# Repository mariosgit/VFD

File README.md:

# VFD

A collection of upcycling projects for Vakuum Fluorescent Displays (VFD). These are Display as you may find in Audio/Video gear like CD/DVD players. A VFD requires high voltage to control anodes and gates, and a small AC voltage for the fillament(heater). To drive each single display element, a time multiplexed controller is required.

## Project Structure...

This is a playground for testing VFDs and there are the PCBs in PCB-KiCAD. See below..

If you only want the display drivers, check out the external repos which are submoduled in the ```./lib``` folder.

```lib/...``` containes submodule display libs and maybe some other local libs which are in development. If a stable status is reached I move them into their own repo.

```src/VFD_TPIC..``` stuff was not integrated into this platformio project yet..

```src/PanelDemo``` is a simple example for a VFD + encoder and button inputs.

```src/FreeDSPController``` is like PanelDemo + it reads some data via I2C from a FreeDSP/ADSP1701. It's a first experiment to use the code generated by SigmaStudio.

### Software Testing

So this is "just" a wrapper PlatformIO project which allows quick switching between the displays I work on.

The thing to be build can be choosen in ```.env``` file. If there is none, copy the ```.env.example```.

### src/main

Is a wrapper into the other sources under ```src``` or into the examples under ```lib/XYZ/examples/...```.

You can also switch between demo programms by commenting in/out the defines.. only one at a time... but using ```.env``` does not infect the git repo.

## PCBs

There are some sub-schematics like VFD-Power which are included in the other schematics.

### MN12832JC-TeensyLC

This is a VFD + 2 Encoders + 2 Switches. (For the FreeDSPController)

Status: Works somewhat, It would have been better with Level shifters. During power up it can show some random noise, due to level issues.

### GP1294AI

This is a board with the VFD + 2 encoders + 10 switches.

#### Status: Experimental, PCB is in development. 

Has some bugs, I2C and I2S on wrong pins... etc.

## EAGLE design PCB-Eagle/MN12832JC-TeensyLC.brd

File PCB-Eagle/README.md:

# Todo:

- Add Power Management
    - PowerSupply (12-24V) -> 5V Step Down Conv.
    - ON/OFF ? at least for the AMPs, or use sleep pins.
- Inputs via 74165 and SPI ? 3+2 Wires (MISO,CLK,LD, NxCE) (see PreenFM/Shruti)
- Add fancy lights
  - Teensy LC has a output for WS2812 (not 3.2, buffer 74LV1T125)
  - Around the encoders - glowing circle.
  - above and below the display

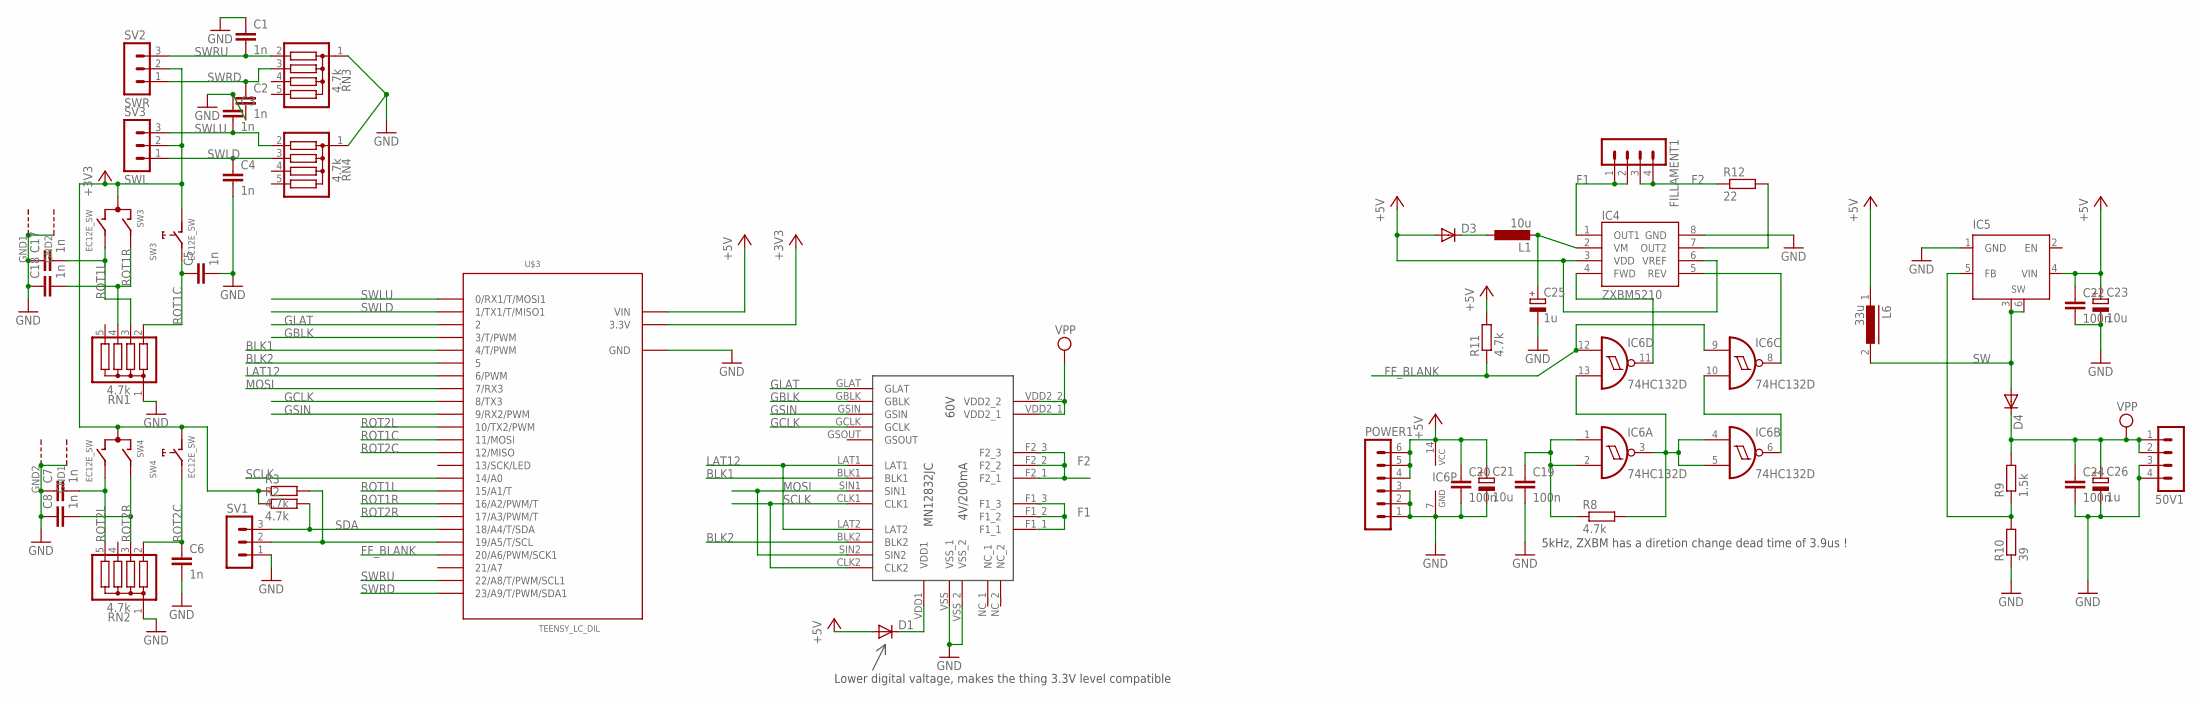
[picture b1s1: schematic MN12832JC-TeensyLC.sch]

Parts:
50V1: MA04-1
C1, C2, C3, C4, C5, C6, C7, C8, C17, C18: 1n; C1206
C19, C20, C22, C24: 100n; C1206
C21, C23: 10u; 153CLV-0807
C25, C26: 1u; 153CLV-0505
D1, D3, D4: DIODE-SMB; SMB
FILLAMENT1: MA04-1
IC4: ZXBM5210; SO8
IC5: XL6009; TO263-5
IC6: 74HC132D; SO14
L1: 10u; L1812
L6: 33u; DR125
POWER1: MA06-1
R2, R3, R8, R11: 4.7k; R1206
R9: 1.5k; R1206
R10: 39; R1206
R12: 22; 0411/15
RN1, RN2, RN3, RN4: 4.7k; SIL5
SV1: MA03-1
SV2: SWR; MA03-1
SV3: SWL; MA03-1
SW3, SW4: EC12E_SW; ALPS_EC12E_SW
U$1: MN12832JC
U$3: TEENSY_LC_DIL; TEENSY_3.0-3.2&LC_DIL

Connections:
+3V3: R2.1, R3.1, SV2.2, SV3.2, SW3.C, SW3.D (1), SW4.C, SW4.D (1), U$3.3.3V
+5V: C20.1, C21.+, C22.1, C23.+, D1.A, D3.A, IC4.3 (VDD), IC4.6 (VREF), IC5.4 (VIN), IC6.14 (VCC), L6.1, POWER1.4, POWER1.5, POWER1.6, R11.2, U$3.VIN
BLK1: U$1.BLK1, U$3.4 (4/T/PWM)
BLK2: U$1.BLK2, U$3.5
F1: FILLAMENT1.1, FILLAMENT1.2, IC4.1 (OUT1), U$1.F1_1, U$1.F1_2, U$1.F1_3
F2: FILLAMENT1.3, FILLAMENT1.4, R12.1, U$1.F2_1, U$1.F2_2, U$1.F2_3
FF_BLANK: IC6.9 (I0), IC6.12 (I0), R11.1, U$3.20/A6 (20/A6/PWM/SCK1)
GBLK: U$1.GBLK, U$3.3 (3/T/PWM)
GCLK: U$1.GCLK, U$3.8 (8/TX3)
GLAT: U$1.GLAT, U$3.2
GND: 50V1.3, 50V1.4, C1.1, C2.2, C3.1, C4.2, C5.2, C6.2, C7.1, C8.1, C17.1, C18.1, C19.2, C20.2, C21.-, C22.2, C23.-, C24.2, C25.-, C26.-, IC4.8 (GND), IC5.1 (GND), IC6.7 (GND), POWER1.1, POWER1.2, POWER1.3, R10.1, RN1.1, RN2.1, RN3.1, RN4.1, SV1.1, SW3.GND1 (G), SW3.GND2 (G), SW4.GND1 (G), SW4.GND2 (G), U$1.VSS (VSS_1), U$1.VSS_2, U$3.AGND (GND), U$3.GND
GSIN: U$1.GSIN, U$3.9 (9/RX2/PWM)
LAT12: U$1.LAT1, U$1.LAT2, U$3.6 (6/PWM)
MOSI: U$1.SIN1, U$1.SIN2, U$3.7 (7/RX3)
unnamed: D1.C, U$1.VDD1
unnamed: C19.1, IC6.1 (I0), IC6.2 (I1), R8.1
unnamed: IC4.5 (REV), IC6.8 (O)
unnamed: D3.C, L1.1
unnamed: C25.+, IC4.2 (VM), L1.2
unnamed: IC6.3 (O), IC6.4 (I0), IC6.5 (I1), IC6.13 (I1), R8.2
unnamed: IC5.5 (FB), R9.1, R10.2
unnamed: IC6.6 (O), IC6.10 (I1)
unnamed: IC4.4 (FWD), IC6.11 (O)
unnamed: IC4.7 (OUT2), R12.2
ROT1C: C5.1, RN1.2, SW3.E (2), U$3.11 (11/MOSI)
ROT1L: C17.2, RN1.3, SW3.B, U$3.15/A1 (15/A1/T)
ROT1R: C18.2, RN1.4, SW3.A, U$3.16/A2 (16/A2/PWM/T)
ROT2C: C6.1, RN2.2, SW4.E (2), U$3.12 (12/MISO)
ROT2L: C7.2, RN2.5, SW4.B, U$3.10 (10/TX2/PWM)
ROT2R: C8.2, RN2.3, SW4.A, U$3.17/A3 (17/A3/PWM/T)
SCL: R3.2, SV1.2, U$3.19/A5 (19/A5/T/SCL)
SCLK: U$1.CLK1, U$1.CLK2, U$3.14/A0
SDA: R2.2, SV1.3, U$3.18/A4 (18/A4/T/SDA)
SW: D4.A, IC5.3 (SW), IC5.6 (SW), L6.2
SWLD: C4.1, RN4.3, SV3.1, U$3.1 (1/TX1/T/MISO1)
SWLU: C3.2, RN4.2, SV3.3, U$3.0 (0/RX1/T/MOSI1)
SWRD: C2.1, RN3.3, SV2.1, U$3.23/A9 (23/A9/T/PWM/SDA1)
SWRU: C1.2, RN3.2, SV2.3, U$3.22/A8 (22/A8/T/PWM/SCL1)
VPP: 50V1.1, 50V1.2, C24.1, C26.+, D4.C, R9.2, U$1.VDD2_1, U$1.VDD2_2

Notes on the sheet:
5kHz, ZXBM has a diretion change dead time of 3.9us !
Lower digital valtage, makes the thing 3.3V level compatible

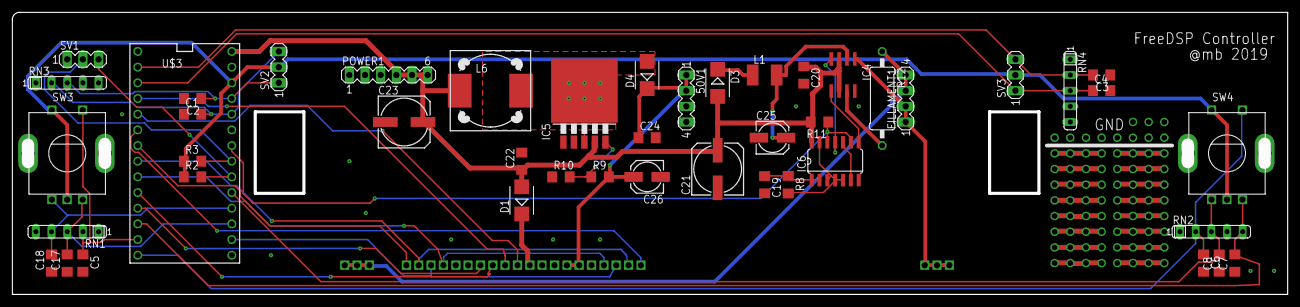
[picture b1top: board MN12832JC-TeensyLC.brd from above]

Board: 2 copper layers, 206.7 x 45.7 mm, 47 parts (1 on the bottom side), 39 nets.

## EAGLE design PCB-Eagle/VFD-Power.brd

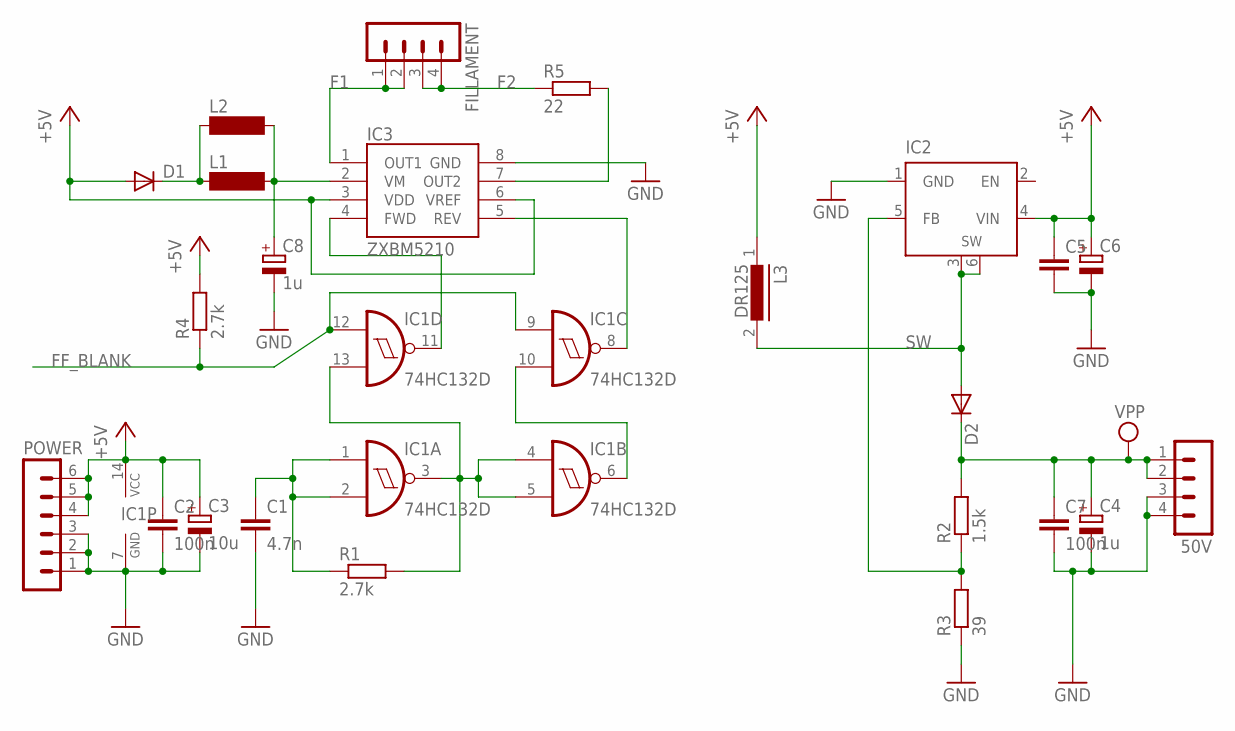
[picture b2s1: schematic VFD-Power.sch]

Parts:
50V: MA04-1
C1: 4.7n; C1206
C2, C7: 100n; C1206
C3: 10u; 153CLV-0807
C4, C8: 1u; 153CLV-0505
C5: C-EUC1206; C1206
C6: CPOL-EU153CLV-0807; 153CLV-0807
D1, D2: DIODE-SMB; SMB
FILLAMENT: MA04-1
IC1: 74HC132D; SO14
IC2: XL6009; TO263-5
IC3: ZXBM5210; SO8
L1: SM-NE45
L2: MS85
L3: DR125
POWER: MA06-1
R1, R4: 2.7k; R1206
R2: 1.5k; R1206
R3: 39; R1206
R5: 22; 0411/15

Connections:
+5V: C2.1, C3.+, C5.1, C6.+, D1.A, IC1.14 (VCC), IC2.4 (VIN), IC3.3 (VDD), IC3.6 (VREF), L3.1, POWER.4, POWER.5, POWER.6, R4.2
F1: FILLAMENT.1, FILLAMENT.2, IC3.1 (OUT1)
F2: FILLAMENT.3, FILLAMENT.4, R5.1
FF_BLANK: IC1.9 (I0), IC1.12 (I0), R4.1
GND: 50V.3, 50V.4, C1.2, C2.2, C3.-, C4.-, C5.2, C6.-, C7.2, C8.-, IC1.7 (GND), IC2.1 (GND), IC3.8 (GND), POWER.1, POWER.2, POWER.3, R3.1
unnamed: IC1.6 (O), IC1.10 (I1)
unnamed: C1.1, IC1.1 (I0), IC1.2 (I1), R1.1
unnamed: IC1.11 (O), IC3.4 (FWD)
unnamed: IC3.7 (OUT2), R5.2
unnamed: IC1.8 (O), IC3.5 (REV)
unnamed: D1.C, L1.1, L2.1
unnamed: C8.+, IC3.2 (VM), L1.2, L2.2
unnamed: IC1.3 (O), IC1.4 (I0), IC1.5 (I1), IC1.13 (I1), R1.2
unnamed: IC2.5 (FB), R2.1, R3.2
SW: D2.A, IC2.3 (SW), IC2.6 (SW), L3.2
VPP: 50V.1, 50V.2, C4.+, C7.1, D2.C, R2.2

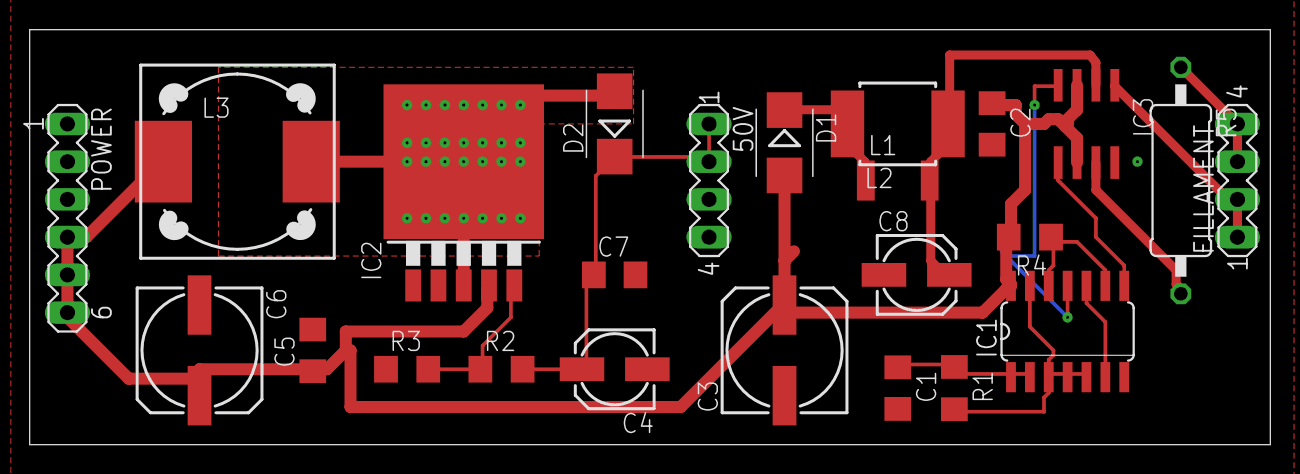
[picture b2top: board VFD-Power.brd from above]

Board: 2 copper layers, 83.5 x 27.9 mm, 24 parts (0 on the bottom side), 16 nets.

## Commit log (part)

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2018-04-25 Initial test program for TPIC6b595.
2018-04-25 Copy of the TPIC code for NEC FIP20D9X
2018-04-26 Update README.md
    Added instructable link.
2018-10-01 A bit more detail..
2018-10-28 It works.
2018-10-28 added image
2018-10-28 moved image
2018-10-28 Added Log lib, used here and there.
2018-10-28 Bit more Doc.
2018-10-28 Optimized, shorter interrupt, brighter display.
2019-01-07 Added some drawing demo code.
2019-01-08 First Attempt to use a STM32F1x. Experimenting with a MN12864.
2019-01-08 Ignore .vscode.
2019-11-10 Added PCBs.
2019-11-10 working on BOM
2019-11-19 Larger Drills for Display
2019-11-19 locked proto area, will not ripup and disappear
2019-11-20 minor stuff
2019-11-20 fixed Up Converter R9/R10 twist, adjusted values for 50V
2019-11-21 set PWM pin to high for the new board.
2019-11-22 Added Voltage drop diode for Vdd1, lowered Fillament frequency to avoid off time
2019-11-26 adapted for use with the AMP1, inital working version
2019-12-01 Rearanged in a bit more Arduino library style.
2019-12-01 sorted out example code vs. Panel code.
2019-12-04 added FreeDSP controller. Reads Levels. Sets Volume.
2019-12-04 LevelMeter+Volume
2019-12-04 Typo, Libpath
2019-12-04 updated readme...
2019-12-04 nicer
2019-12-04 todo list...
2019-12-04 more todo
2019-12-09 Waiting for I2C silence after boot.
2024-01-08 Freedom for makers !
2024-01-08 kicad ignore update.
2024-01-10 Progress on GP1294 board..
2024-01-15 GP1294 progress..
2024-01-16 GP1294 progress...
2024-01-18 GP1294...
2024-01-18 GP1294 more progress...
2024-01-21 more progress
2024-01-22 GP12.. better case and stuff
2024-01-23 ATtiny software for input control.
2024-01-29 GP1294 evolves
2024-01-31 Starting GP1294 software
2024-01-31 GP1294 stuff..
2024-02-01 Added SRC.
2024-02-01 grummel
2024-02-01 Fixed merge issues.
2024-02-02 nix.
2024-02-08 Added OLED 5.5" option
2024-02-09 Upgraded Power circuit.
2024-02-09 Added test code for GP1294
2024-02-12 Added Debounce Caps and stuff.
2024-02-15 README updated, restructuring..
2024-02-15 Rearranged into PlatformIO project.
2024-02-15 missing peaces..
2024-02-15 Experiments with MN12832L...
2024-02-16 Progress...
2024-02-16 Added Odd/Even buffers.
2024-02-16 Breakpoint, looking better, but only one gate active.
2024-02-16 Breakpoint, ok, just the seams...
2024-02-16 Nicer Demo
2024-02-16 Somewhat useable...
2024-02-19 Replaced dualbuffer with masking.
2024-02-19 Added doubl buffer.
2024-02-19 Runs with serial 1->2 chain.
2024-02-19 breakpoint, shift out 2x for serial in chain.
2024-02-19 Added greyscale.
2024-02-19 README merge.
2024-02-19 Moved MN12832L to own repo.
2024-02-19 still..
2024-02-19 Updated README.
2024-02-21 Progress with MN12832L...
2024-02-22 Compile on STM32
2024-02-22 Working on MN12864K...
2024-02-23 Experiments with MN12864K...
2024-02-23 Can change build example by .env file.
2024-02-23 Not much..
2024-02-23 Cleaned up readme.
2024-02-23 Stuff
2024-02-23 Fixing git..
2024-02-23 Readded subrepo.
2024-02-23 Readded subrepo 2
2024-02-23 Progress with MN12864K.
2024-02-26 drawFastHLine...
2024-02-26 Cleanup.
2024-02-26 Better.
2024-02-28 Added lib/font and example under MN12832L
2024-03-05 PCB: TestPin must pull up with 100k.
2024-03-05 More GP1294 experiments and stuff.
2024-03-06 Nicer Demo.
2024-03-06 hkgkgk
2024-03-07 GP1294 board, added light and remote sensors.
2024-03-07 Fixed merge fail.
2024-03-12 input test..
2024-03-14 Fixed i2c..
2024-03-27 Some silkscreen fixes.
2024-03-27 Input: Minifix
2024-05-23 Checks and Firmware after 1st build.
2024-05-27 Removed confusing stuff
2024-05-27 Trouble with submodules...
2024-06-10 Threads for all.
2024-06-19 Updated case for 3d print.
2024-08-30 GP1291 fixes, removed input mcu, added SRCs.
2024-08-30 Updated README todo list.
2024-09-18 Added new HUI panel with MN12832L
2024-09-18 Updated README..
2024-09-29 Beauty fixes
2024-10-01 tests with new MN12832L panel.
2024-10-01 Added FreeDSPControllerMN12832L
2024-10-02 More stuff for MN12832L-panel
2024-10-05 Going back to teensylc.
2024-10-05 Some fixes..
2024-10-05 More fixes
2024-10-05 Case update.
2024-10-06 More Case
2024-10-10 Added distortion encoder.
2024-10-11 Moved some stuff to SigmaDSP lib.
2024-10-11 Moved more stuff to SigmaDSP lib
2024-10-14 Tested TeensyAudio biquad calc, it's useable.
2024-10-15 FreeDSPCtlMN12832L as good as done.
2024-10-15 Minor fixes
2024-10-17 Added Crossover and some stuff.
2024-10-17 Added log of crossover params.
2024-10-18 Changed some preset dsp values, fixed input?
2024-10-21 EQ and stuff for W3 fast chassis.
2024-10-30 temp..
2024-10-30 Checked, fixed timing.
2024-10-31 Upgraded to 8 band EQ.
2024-10-31 Added some peak checkers and compression.
2024-10-31 Reading the readback stuff....
2024-11-02 Changed EQ and Speki to 9 bands.
